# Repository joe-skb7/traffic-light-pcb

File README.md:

# "Traffic Light" system: hardware design files

Hardware files for traffic light model and interfacing board.

Corresponding software for controlling the interface board can be found at [1].

## Photo

Interfacing board, top view:

Interfacing board, bottom view:

Traffic light board:

## Overview

This repository consists of two KiCad projects:

1. Traffic light board (`light/*`):
   - it has 5 red and 5 green LEDs on it
2. Interfacing board (`iface/*`):
   - connect it to your PC (via USB cable) from one side
   - connect it to up to 10 traffic light boards (via phone cable) from other
     side

Kicad v5.0.1 was used.

You can find exported schematics in PDF format in `doc/output/` directory.

Once connected, use libtrl [1] to control traffic light boards via interface
board.

## Authors

**Sam Protsenko**

## License

This project is licensed under the GPLv3.

## References

[1] https://github.com/joe-skb7/libtrl

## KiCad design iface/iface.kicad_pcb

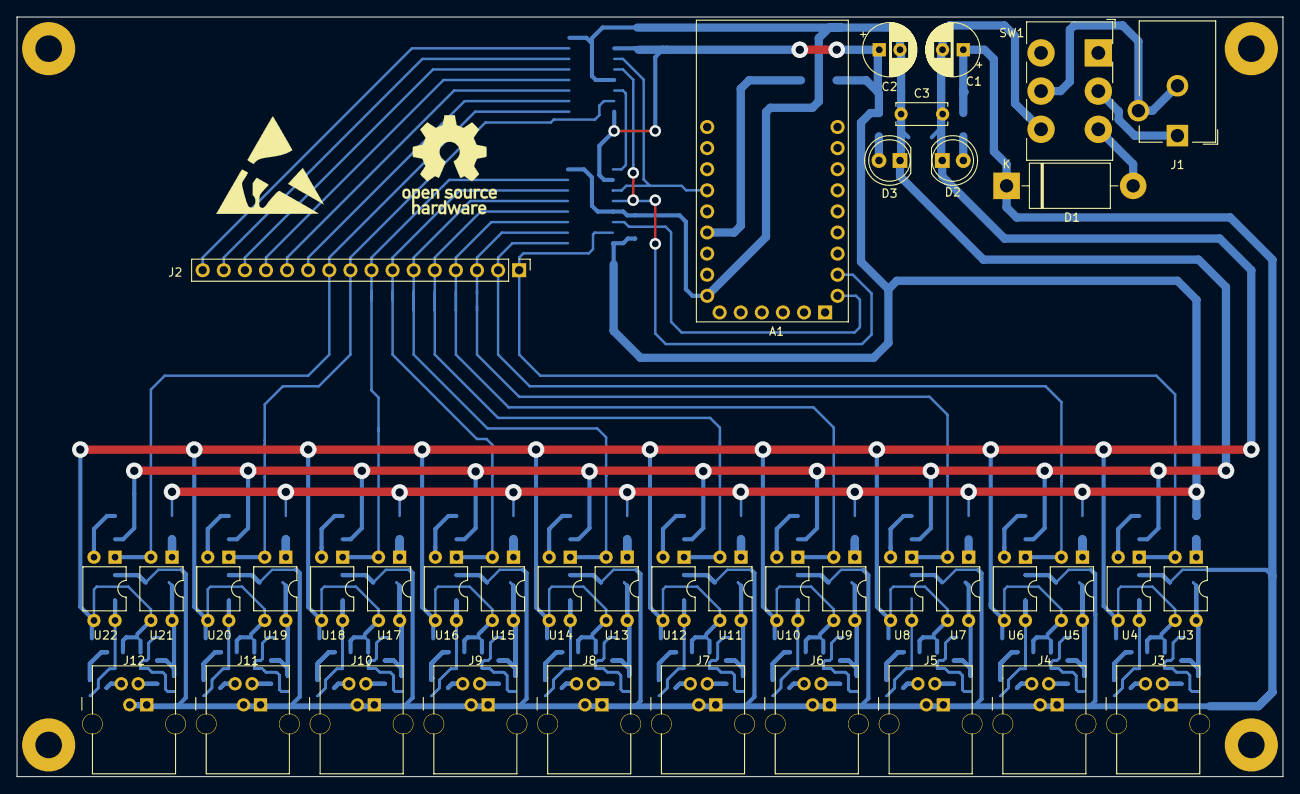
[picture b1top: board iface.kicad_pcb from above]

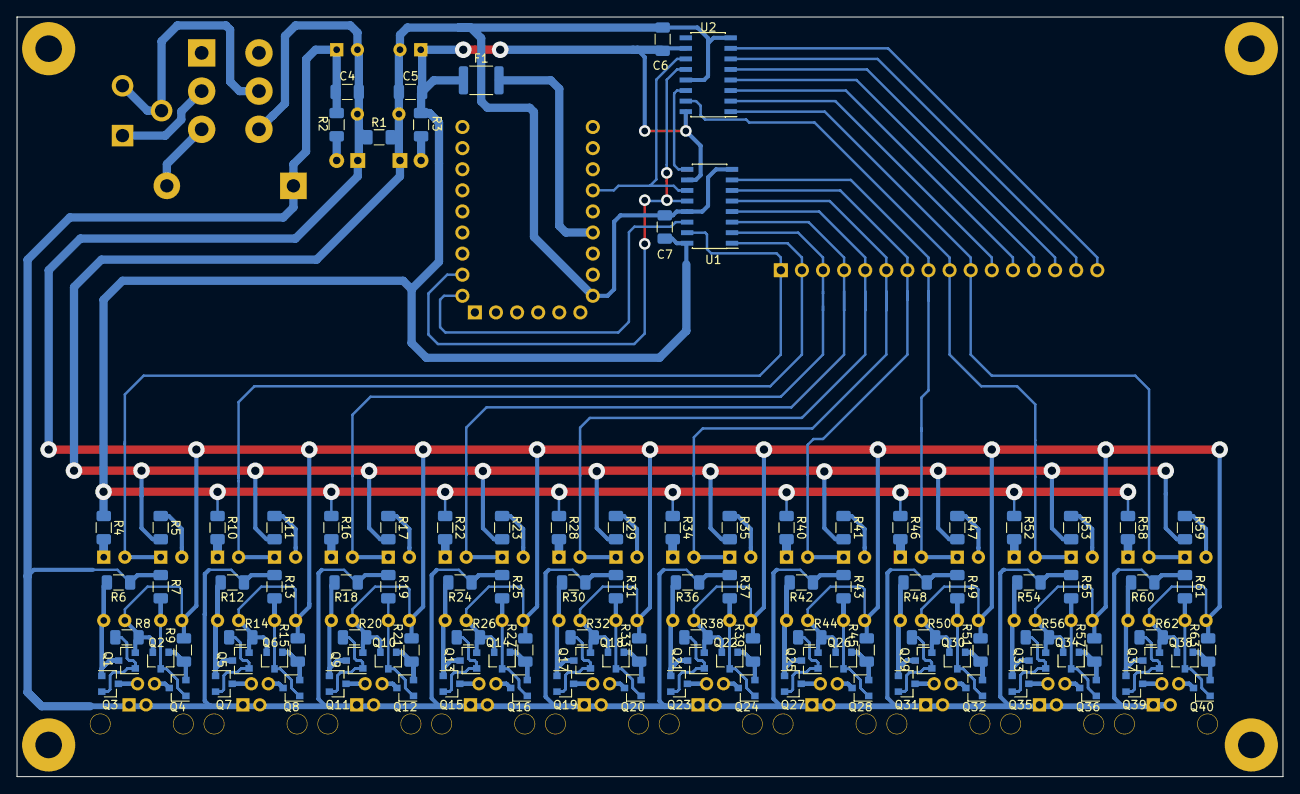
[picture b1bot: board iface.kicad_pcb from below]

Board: 2 copper layers, 152.4 x 91.4 mm, 156 parts (110 on the bottom side), 110 nets.

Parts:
A1: FTDI232
C1, C2: 100uF/25V; CP_Radial_D6.3mm_P2.50mm
C3: 1nF/2kV; C_Disc_D6.0mm_W2.5mm_P5.00mm
C4, C5, C6, C7: 100nF; C_1206_3216Metric
D1: 1N5822; D_DO-201AD_P15.24mm_Horizontal
D2: YELLOW; LED_D5.0mm
D3: RED; LED_D5.0mm
F1: Polyfuse; Fuse_1812_4532Metric
H1, H2, H3, H4: MountingHole_Pad; MountingHole_3.2mm_M3_Pad
J1: Barrel_Jack_Switch; BarrelJack_CUI_PJ-102AH_Horizontal
J2: Conn_01x16; PinHeader_1x16_P2.54mm_Vertical
J3, J4, J5, J6, J7, J8, J9, J10, J11, J12: 4P4C; RJ9_KLS_12-123-4P
Q1, Q2, Q3, Q4, Q5, Q6, Q7, Q8, Q9, Q10, Q11, Q12, Q13, Q14, Q15, Q16, Q17, Q18, Q19, Q20, Q21, Q22, Q23, Q24, Q25, Q26, Q27, Q28, Q29, Q30, Q31, Q32, Q33, Q34, Q35, Q36, Q37, Q38, Q39, Q40: BC847; SOT-23
R1: 1M; R_1206_3216Metric
R2: 820R; R_1206_3216Metric
R3: 330R; R_1206_3216Metric
R4, R5, R10, R11, R16, R17, R22, R23, R28, R29, R34, R35, R40, R41, R46, R47, R52, R53, R58, R59: 470R; R_1206_3216Metric
R6, R7, R12, R13, R18, R19, R24, R25, R30, R31, R36, R37, R42, R43, R48, R49, R54, R55, R60, R61: 10k; R_1206_3216Metric
R8, R9, R14, R15, R20, R21, R26, R27, R32, R33, R38, R39, R44, R45, R50, R51, R56, R57, R62, R63: 39R; R_1206_3216Metric
SW1: SW_DPDT_x2; SW_CW_GF-126-0305_DPDT
SYM1: SYM_ESD_Large; ESD-Logo_13.2x12mm_SilkScreen
SYM2: Logo_Open_Hardware_Small; OSHW-Logo_11.4x12mm_SilkScreen
U1, U2: 74HC595; SOIC-16_3.9x9.9mm_P1.27mm
U3, U4, U5, U6, U7, U8, U9, U10, U11, U12, U13, U14, U15, U16, U17, U18, U19, U20, U21, U22: PC817; DIP-4_W7.62mm

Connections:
+5V: C2.1, C5.1, C6.1, C7.1, F1.1, R3.2, R4.2, R10.2, R16.2, R22.2, R28.2, R34.2, R40.2, R46.2, R52.2, R58.2, U1.10, U1.16, U2.10, U2.16
+12V: C1.1, C4.1, D1.1, J3.1, J3.3, J4.1, J4.3, J5.1, J5.3, J6.1, J6.3, J7.1, J7.3, J8.1, J8.3, J9.1, J9.3, J10.1, J10.3, J11.1, J11.3, J12.1, J12.3, R2.2, R6.1, R7.1, R12.1, R13.1, R18.1, R19.1, R24.1, R25.1, R30.1, R31.1, R36.1, R37.1, R42.1, R43.1, R48.1, R49.1, R54.1, R55.1, R60.1, R61.1
/D0: J2.1, U1.15, U3.2, U4.1
/D1: J2.2, U1.1, U5.2, U6.1
/D2: J2.3, U1.2, U7.2, U8.1
/D3: J2.4, U1.3, U9.2, U10.1
/D4: J2.5, U1.4, U11.2, U12.1
/D5: J2.6, U1.5, U13.2, U14.1
/D6: J2.7, U1.6, U15.2, U16.1
/D7: J2.8, U1.7, U17.2, U18.1
/D8: J2.9, U2.15, U19.2, U20.1
/D9: J2.10, U2.1, U21.2, U22.1
/Logic/CLOCK: A1.12, U1.11, U2.11
/Logic/D10: J2.11, U2.2
/Logic/D11: J2.12, U2.3
/Logic/D12: J2.13, U2.4
/Logic/D13: J2.14, U2.5
/Logic/D14: J2.15, U2.6
/Logic/D15: J2.16, U2.7
/Logic/DATA: A1.16, U1.14
/Logic/LATCH: A1.17, U1.12, U2.12
FTDI_5V: A1.10, F1.2
GNDD: A1.7, C2.2, C3.1, C5.2, C6.2, C7.2, D3.1, R1.1, R5.1, R11.1, R17.1, R23.1, R29.1, R35.1, R41.1, R47.1, R53.1, R59.1, U1.8, U1.13, U2.8, U2.13
GNDPWR: C1.2, C3.2, C4.2, D2.1, H1.1, H2.1, H3.1, H4.1, Q1.2, Q2.2, Q5.2, Q6.2, Q9.2, Q10.2, Q13.2, Q14.2, Q17.2, Q18.2, Q21.2, Q22.2, Q25.2, Q26.2, Q29.2, Q30.2, Q33.2, Q34.2, Q37.2, Q38.2, R1.2, R8.2, R9.2, R14.2, R15.2, R20.2, R21.2, R26.2, R27.2, R32.2, R33.2, R38.2, R39.2, R44.2, R45.2, R50.2, R51.2, R56.2, R57.2, R62.2, R63.2, SW1.6, U3.3, U4.3, U5.3, U6.3, U7.3, U8.3, U9.3, U10.3, U11.3, U12.3, U13.3, U14.3, U15.3, U16.3, U17.3, U18.3, U19.3, U20.3, U21.3, U22.3
unnamed: D1.2, SW1.3
unnamed: D2.2, R2.1
unnamed: D3.2, R3.1
unnamed: J1.1, SW1.2
unnamed: J1.2, J1.3, SW1.5
unnamed: J3.2, Q3.3
unnamed: J3.4, Q4.3
unnamed: J4.2, Q7.3
unnamed: J4.4, Q8.3
unnamed: J5.2, Q11.3
unnamed: J5.4, Q12.3
unnamed: J6.2, Q15.3
unnamed: J6.4, Q16.3
unnamed: J7.2, Q19.3
unnamed: J7.4, Q20.3
unnamed: J8.2, Q23.3
unnamed: J8.4, Q24.3
unnamed: J9.2, Q27.3
unnamed: J9.4, Q28.3
unnamed: J10.2, Q31.3
unnamed: J10.4, Q32.3
unnamed: J11.2, Q35.3
unnamed: J11.4, Q36.3
unnamed: J12.2, Q39.3
unnamed: J12.4, Q40.3
unnamed: Q1.1, Q3.2, R8.1
unnamed: Q1.3, Q3.1, R6.2, U3.4
unnamed: Q2.1, Q4.2, R9.1
unnamed: Q2.3, Q4.1, R7.2, U4.4
unnamed: Q5.1, Q7.2, R14.1
unnamed: Q5.3, Q7.1, R12.2, U5.4
unnamed: Q6.1, Q8.2, R15.1
unnamed: Q6.3, Q8.1, R13.2, U6.4
unnamed: Q10.1, Q12.2, R21.1
unnamed: Q10.3, Q12.1, R19.2, U8.4
unnamed: Q9.3, Q11.1, R18.2, U7.4
unnamed: Q9.1, Q11.2, R20.1
unnamed: Q13.1, Q15.2, R26.1
unnamed: Q13.3, Q15.1, R24.2, U9.4
unnamed: Q14.1, Q16.2, R27.1
unnamed: Q14.3, Q16.1, R25.2, U10.4
unnamed: Q17.1, Q19.2, R32.1
unnamed: Q17.3, Q19.1, R30.2, U11.4
unnamed: Q18.1, Q20.2, R33.1
unnamed: Q18.3, Q20.1, R31.2, U12.4
unnamed: Q21.1, Q23.2, R38.1
unnamed: Q21.3, Q23.1, R36.2, U13.4
unnamed: Q22.1, Q24.2, R39.1
unnamed: Q22.3, Q24.1, R37.2, U14.4
unnamed: Q25.1, Q27.2, R44.1
unnamed: Q25.3, Q27.1, R42.2, U15.4
unnamed: Q26.1, Q28.2, R45.1
unnamed: Q26.3, Q28.1, R43.2, U16.4
unnamed: Q29.1, Q31.2, R50.1
unnamed: Q29.3, Q31.1, R48.2, U17.4
unnamed: Q30.1, Q32.2, R51.1
unnamed: Q30.3, Q32.1, R49.2, U18.4
unnamed: Q33.1, Q35.2, R56.1
unnamed: Q33.3, Q35.1, R54.2, U19.4
unnamed: Q34.1, Q36.2, R57.1
unnamed: Q34.3, Q36.1, R55.2, U20.4
unnamed: Q37.1, Q39.2, R62.1
unnamed: Q37.3, Q39.1, R60.2, U21.4
unnamed: Q38.1, Q40.2, R63.1
unnamed: Q38.3, Q40.1, R61.2, U22.4
unnamed: R4.1, U3.1
unnamed: R5.2, U4.2
unnamed: R10.1, U5.1
unnamed: R11.2, U6.2
unnamed: R16.1, U7.1
unnamed: R17.2, U8.2
unnamed: R22.1, U9.1
unnamed: R23.2, U10.2
unnamed: R28.1, U11.1
unnamed: R29.2, U12.2
unnamed: R34.1, U13.1
unnamed: R35.2, U14.2
unnamed: R40.1, U15.1
unnamed: R41.2, U16.2
unnamed: R46.1, U17.1
unnamed: R47.2, U18.2
unnamed: R52.1, U19.1
unnamed: R53.2, U20.2
unnamed: R58.1, U21.1
unnamed: R59.2, U22.2
unnamed: U1.9, U2.14

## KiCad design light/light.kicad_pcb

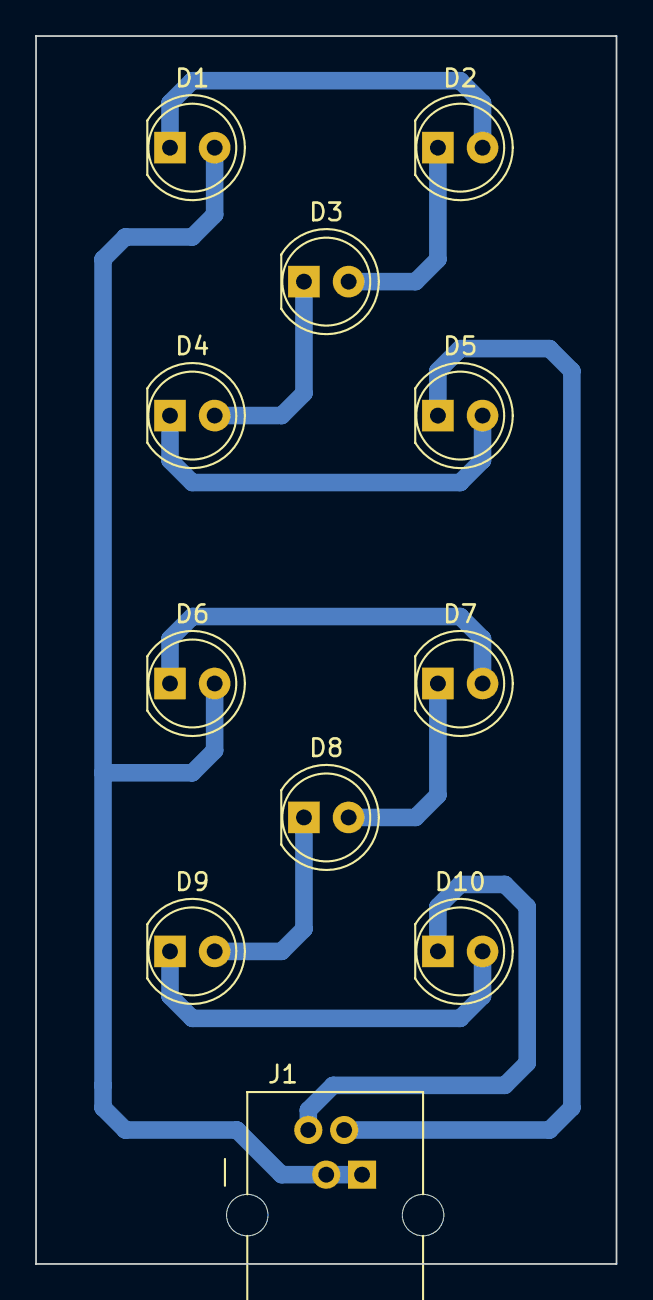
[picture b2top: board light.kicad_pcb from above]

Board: 2 copper layers, 33.0 x 69.8 mm, 11 parts (0 on the bottom side), 11 nets.

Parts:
D1, D2, D3, D4, D5: Red; LED_D5.0mm
D6, D7, D8, D9, D10: Green; LED_D5.0mm
J1: 4P4C; RJ9_KLS_12-123-4P

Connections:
unnamed: D1.1, D2.2
unnamed: D1.2, D6.2, J1.1, J1.3
unnamed: D2.1, D3.2
unnamed: D3.1, D4.2
unnamed: D4.1, D5.2
unnamed: D5.1, J1.2
unnamed: D6.1, D7.2
unnamed: D7.1, D8.2
unnamed: D8.1, D9.2
unnamed: D10.1, J1.4
unnamed: D9.1, D10.2

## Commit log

2018-11-24 Add gitignore file
2018-11-24 doc: Add doc files
2018-11-24 lib: Add footprint for 4P4C (RJ9) jack connector
    Will be used further for interface board.
2018-11-24 light: Add KiCad project for traffic light PCB
2018-11-24 iface: Add KiCad project for interface board
    Initial files. Work is still in progress.
2018-11-24 README: Add mentioning of libtrl
2018-11-27 light: Finish scheme and PCB
2018-11-27 doc: Add traffic light PCB in PDF for toner transfer method
2018-11-28 lib: Add symbol and footprint for FTDI232 module
2018-11-28 lib: Add symbol and footprint for MP1584 module
2018-11-28 light: Add info about local footprint
2018-11-28 iface: Add info about local symbols
2018-11-28 iface: Add info about local footprints
2018-11-28 iface: Continue working on schematic
2018-11-29 lib: mp1584: Fix power output pins
2018-11-29 iface: Finish schematic
2018-11-30 iface: schematic: Final edits
2018-12-01 lib: Improve FTDI232 module
2018-12-01 lib: Improve MP1584 module
2018-12-01 lib: Add footprint for my DPDT switch
2018-12-01 iface: scheme: Add DPDT switch
2018-12-02 light: Use two pins of RJ9 to pass +12V
2018-12-02 .gitignore: Update ignore rules
2018-12-02 iface: Re-wire FTDI232 lines and add some notes to power scheme
2018-12-02 iface: Start routing PCB layout
2018-12-02 doc: Remove outdated file
2018-12-02 README: Add some more info
2018-12-03 lib: mp1584: Fix pins type
2018-12-03 iface: Use different kind of grounds
2018-12-04 lib: Update FTDI232 module
2018-12-04 iface: Simplify schematic
    Apply next changes in order to simplify schematics:
    - use wired logic on optocoupler inputs to get inverted signal;
    driver.sch files was modified; this way we can get rid of two
    inverters (74HC04)
    - use 5V line from USB; this way we can get rid from buck-boost DC-DC
    converter module (MP1584)
2018-12-04 iface: Finish routing the PCB layout
2018-12-05 iface: Update PCB for toner transfer method
2018-12-05 TODO: Add TODO list
2018-12-05 iface: Add description for used Polyfuse
2018-12-05 iface: Fix notes on power scheme
2018-12-05 TODO: Add TODO note
2018-12-07 output: Add exported schematics
2018-12-08 Move PDF schematics to doc/
2018-12-08 README: Add photos
2018-12-08 README: Improve the title
2018-12-12 TODO: Add some items
2019-01-02 iface: schematic: Fix resistor designators on driver sheets
    Fixes: #1
2024-08-24 README: Mention KiCad version used to create schematics and PCB
